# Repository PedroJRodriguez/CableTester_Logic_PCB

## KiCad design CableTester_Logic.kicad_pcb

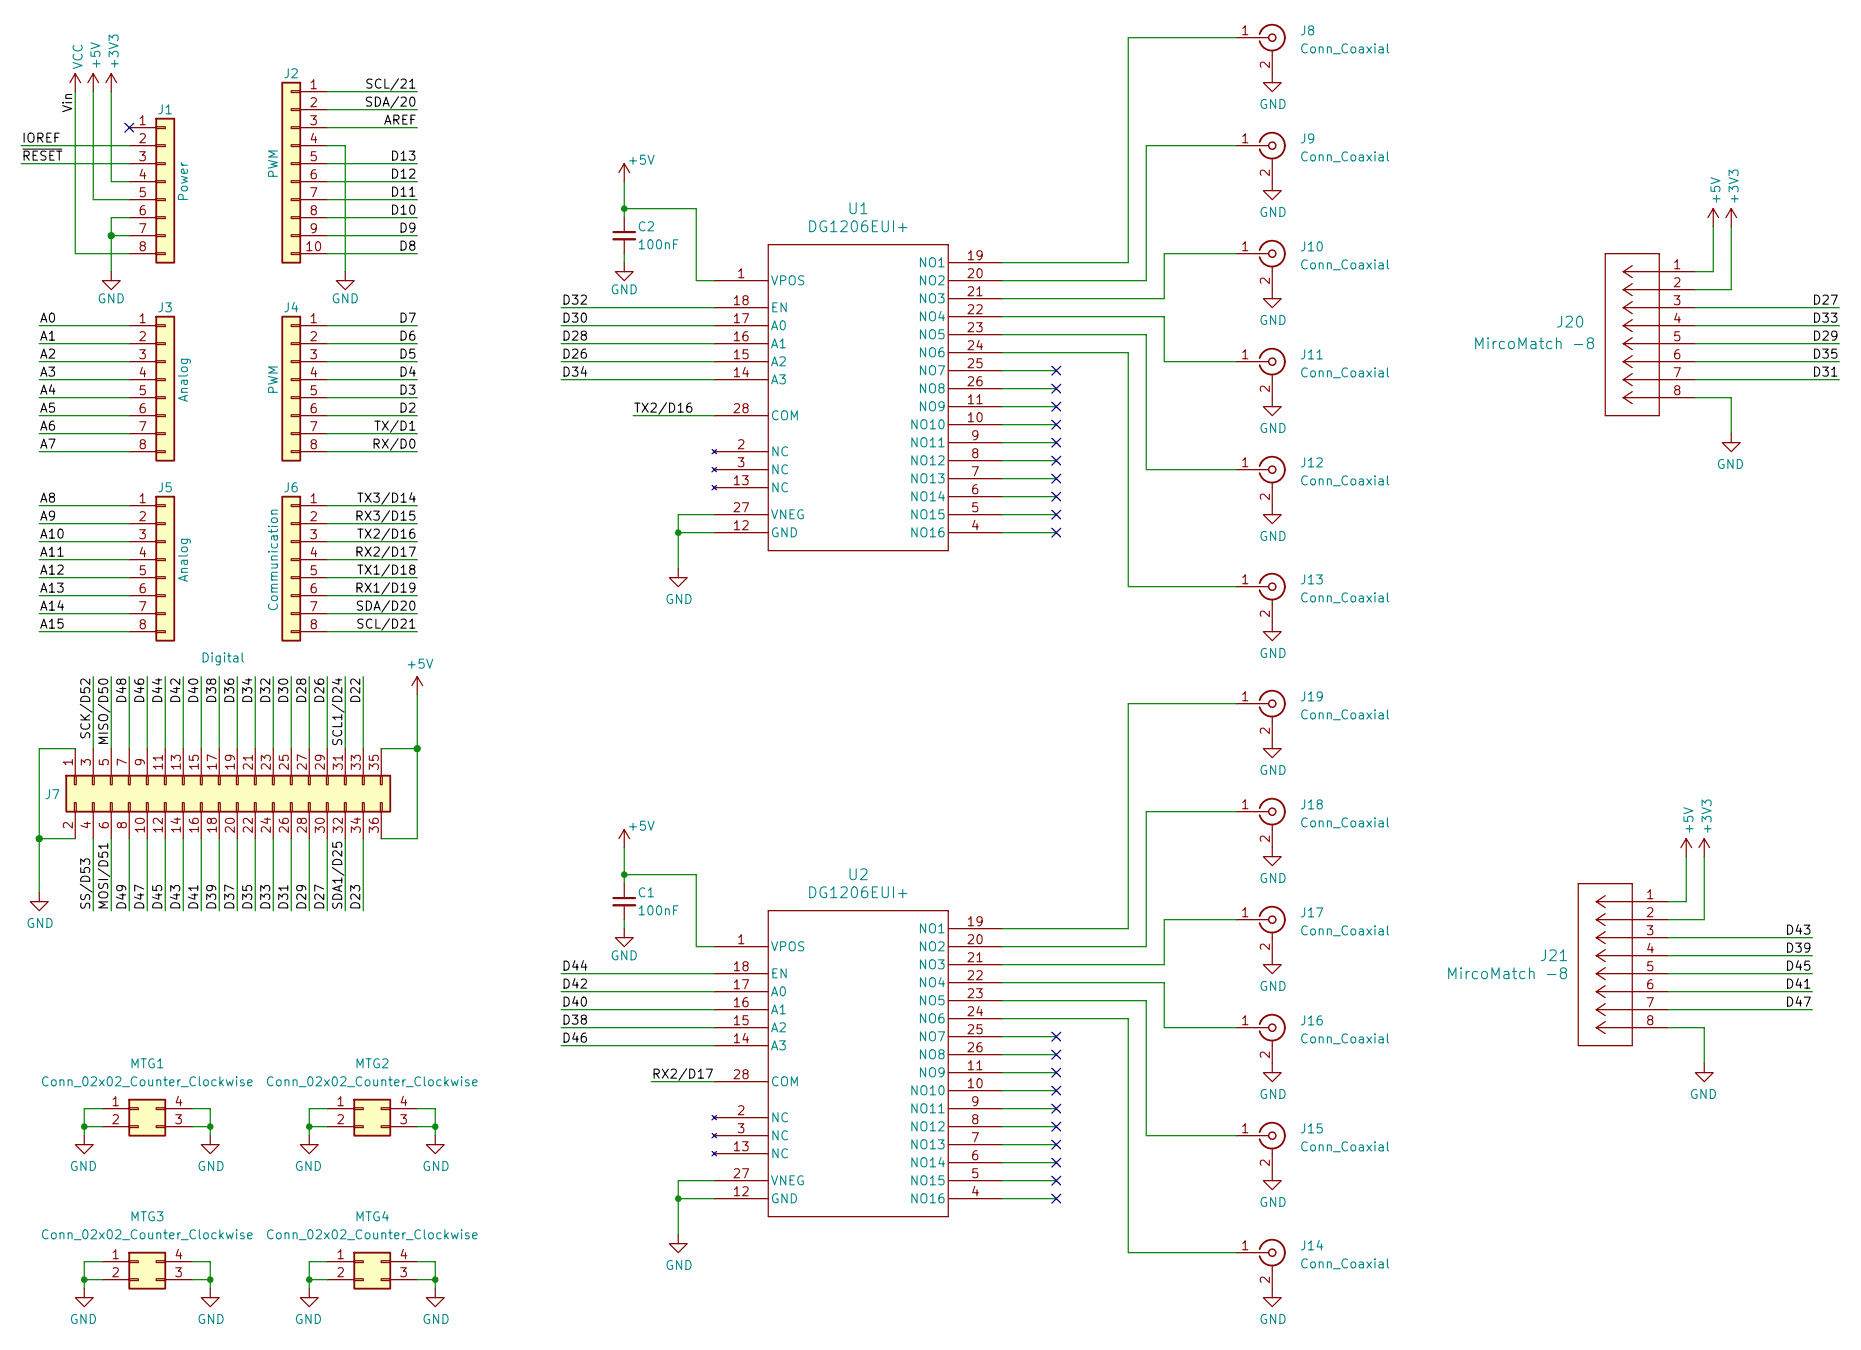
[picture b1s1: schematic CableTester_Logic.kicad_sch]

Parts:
C1, C2: 100nF; C_0805_2012Metric_Pad1.18x1.45mm_HandSolder
J1: Power; PinSocket_1x08_P2.54mm_Vertical
J2: PWM; PinSocket_1x10_P2.54mm_Vertical
J3, J5: Analog; PinSocket_1x08_P2.54mm_Vertical
J4: PWM; PinSocket_1x08_P2.54mm_Vertical
J6: Communication; PinSocket_1x08_P2.54mm_Vertical
J7: Digital; PinSocket_2x18_P2.54mm_Vertical
J8, J9, J10, J11, J12, J13, J14, J15, J16, J17, J18, J19: Conn_Coaxial; SMB_Jack_Vertical
J20, J21: MircoMatch -8; CONN_7-188275-8_TYC
MTG1, MTG2, MTG3, MTG4: Conn_02x02_Counter_Clockwise; KEYSTONE_7693-5
U1, U2: DG1206EUI+; TSSOP-28_4.4x9.7mm_P0.65mm

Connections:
+3V3: J1.4, J20.2, J21.2
+5V: C1.1, C2.1, J1.5, J7.35, J7.36, J20.1, J21.1, U1.1 (VPOS), U2.1 (VPOS)
/A0: J3.1
/A1: J3.2
/A2: J3.3
/A3: J3.4
/A4: J3.5
/A5: J3.6
/A6: J3.7
/A7: J3.8
/A8: J5.1
/A9: J5.2
/A10: J5.3
/A11: J5.4
/A12: J5.5
/A13: J5.6
/A14: J5.7
/A15: J5.8
/AREF: J2.3
/D2: J4.6
/D3: J4.5
/D4: J4.4
/D5: J4.3
/D6: J4.2
/D7: J4.1
/D8: J2.10
/D9: J2.9
/D10: J2.8
/D11: J2.7
/D12: J2.6
/D13: J2.5
/D22: J7.33
/D23: J7.34
/D26: J7.29, U1.15 (A2)
/D27: J7.30, J20.3
/D28: J7.27, U1.16 (A1)
/D29: J7.28, J20.5
/D30: J7.25, U1.17 (A0)
/D31: J7.26, J20.7
/D32: J7.23, U1.18 (EN)
/D33: J7.24, J20.4
/D34: J7.21, U1.14 (A3)
/D35: J7.22, J20.6
/D36: J7.19
/D37: J7.20
/D38: J7.17, U2.15 (A2)
/D39: J7.18, J21.4
/D40: J7.15, U2.16 (A1)
/D41: J7.16, J21.6
/D42: J7.13, U2.17 (A0)
/D43: J7.14, J21.3
/D44: J7.11, U2.18 (EN)
/D45: J7.12, J21.5
/D46: J7.9, U2.14 (A3)
/D47: J7.10, J21.7
/D48: J7.7
/D49: J7.8
/IOREF: J1.2
/MISO/D50: J7.5
/MOSI/D51: J7.6
/RX1/D19: J6.6
/RX2/D17: J6.4, U2.28 (COM)
/RX3/D15: J6.2
/RX/D0: J4.8
/SCK/D52: J7.3
/SCL1/D24: J7.31
/SCL/21: J2.1
/SCL/D21: J6.8
/SDA1/D25: J7.32
/SDA/20: J2.2
/SDA/D20: J6.7
/SS/D53: J7.4
/TX1/D18: J6.5
/TX2/D16: J6.3, U1.28 (COM)
/TX3/D14: J6.1
/TX/D1: J4.7
/~RESET: J1.3
GND: C1.2, C2.2, J1.6, J1.7, J2.4, J7.1, J7.2, J8.2 (Ext), J8.3 (Ext), J8.4 (Ext), J8.5 (Ext), J9.2 (Ext), J9.3 (Ext), J9.4 (Ext), J9.5 (Ext), J10.2 (Ext), J10.3 (Ext), J10.4 (Ext), J10.5 (Ext), J11.2 (Ext), J11.3 (Ext), J11.4 (Ext), J11.5 (Ext), J12.2 (Ext), J12.3 (Ext), J12.4 (Ext), J12.5 (Ext), J13.2 (Ext), J13.3 (Ext), J13.4 (Ext), J13.5 (Ext), J14.2 (Ext), J14.3 (Ext), J14.4 (Ext), J14.5 (Ext), J15.2 (Ext), J15.3 (Ext), J15.4 (Ext), J15.5 (Ext), J16.2 (Ext), J16.3 (Ext), J16.4 (Ext), J16.5 (Ext), J17.2 (Ext), J17.3 (Ext), J17.4 (Ext), J17.5 (Ext), J18.2 (Ext), J18.3 (Ext), J18.4 (Ext), J18.5 (Ext), J19.2 (Ext), J19.3 (Ext), J19.4 (Ext), J19.5 (Ext), J20.8, J21.8, MTG1.1, MTG1.2, MTG1.3, MTG1.4, MTG2.1, MTG2.2, MTG2.3, MTG2.4, MTG3.1, MTG3.2, MTG3.3, MTG3.4, MTG4.1, MTG4.2, MTG4.3, MTG4.4, U1.12 (GND), U1.27 (VNEG), U2.12 (GND), U2.27 (VNEG)
unnamed: J8.1 (In), U1.19 (NO1)
unnamed: J9.1 (In), U1.20 (NO2)
unnamed: J10.1 (In), U1.21 (NO3)
unnamed: J11.1 (In), U1.22 (NO4)
unnamed: J12.1 (In), U1.23 (NO5)
unnamed: J13.1 (In), U1.24 (NO6)
unnamed: J14.1 (In), U2.24 (NO6)
unnamed: J15.1 (In), U2.23 (NO5)
unnamed: J16.1 (In), U2.22 (NO4)
unnamed: J17.1 (In), U2.21 (NO3)
unnamed: J18.1 (In), U2.20 (NO2)
unnamed: J19.1 (In), U2.19 (NO1)
VCC: J1.8

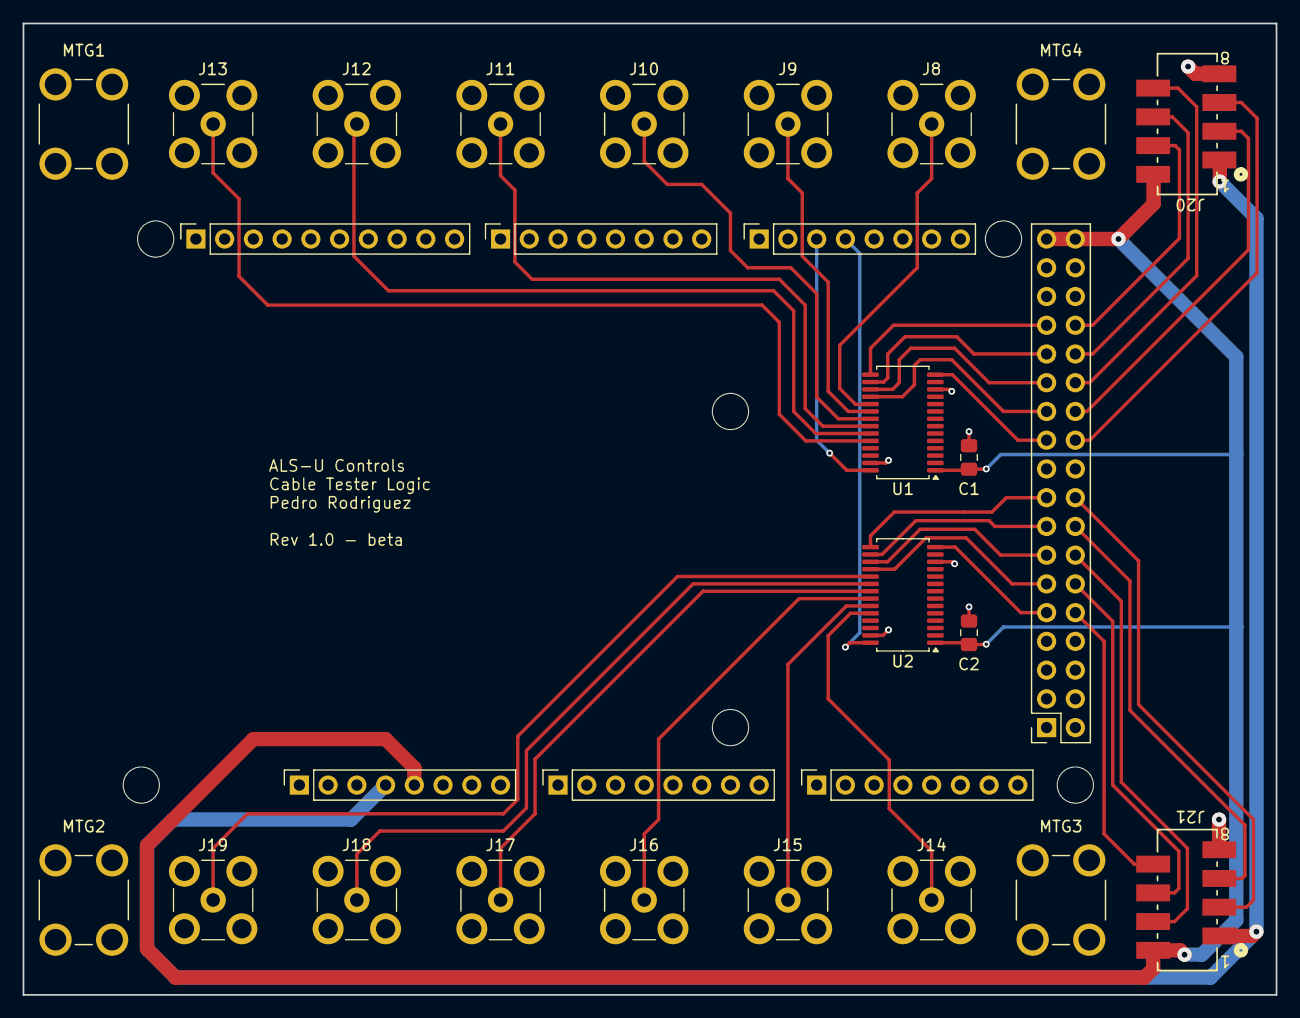
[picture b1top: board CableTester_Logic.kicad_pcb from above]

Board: 2 copper layers, 110.7 x 85.9 mm, 35 parts (0 on the bottom side), 37 nets.

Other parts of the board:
MH1, MH2, MH3, MH4, MH5, MH6: MountingHole_3.2mm

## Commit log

2025-09-03 Initial Commit of Basic Layout and Parts
2025-09-14 updated schamtic
    updated schamtic
2025-09-17 Finalized Project for Test Production
